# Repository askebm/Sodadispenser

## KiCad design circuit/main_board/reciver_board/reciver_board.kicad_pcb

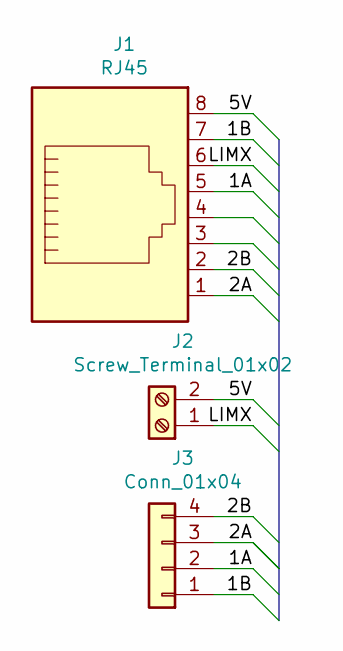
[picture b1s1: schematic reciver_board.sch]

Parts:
J1: RJ45; RJ45_Wuerth_7499010121A_Horizontal
J2: Screw_Terminal_01x02; TerminalBlock_Altech_AK300-2_P5.00mm
J3: Conn_01x04; PinSocket_1x04_P2.54mm_Vertical

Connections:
/1A: J1.5, J3.2
/1B: J1.7, J3.1
/2A: J1.1, J3.3
/2B: J1.2, J3.4
/5V: J1.8, J2.2
/LIMX: J1.6, J2.1

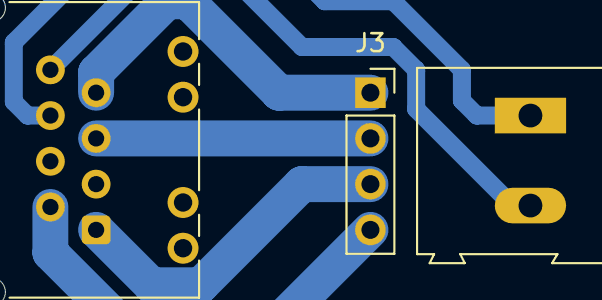
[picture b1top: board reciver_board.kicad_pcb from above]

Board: 2 copper layers, 3 parts (0 on the bottom side), 6 nets.

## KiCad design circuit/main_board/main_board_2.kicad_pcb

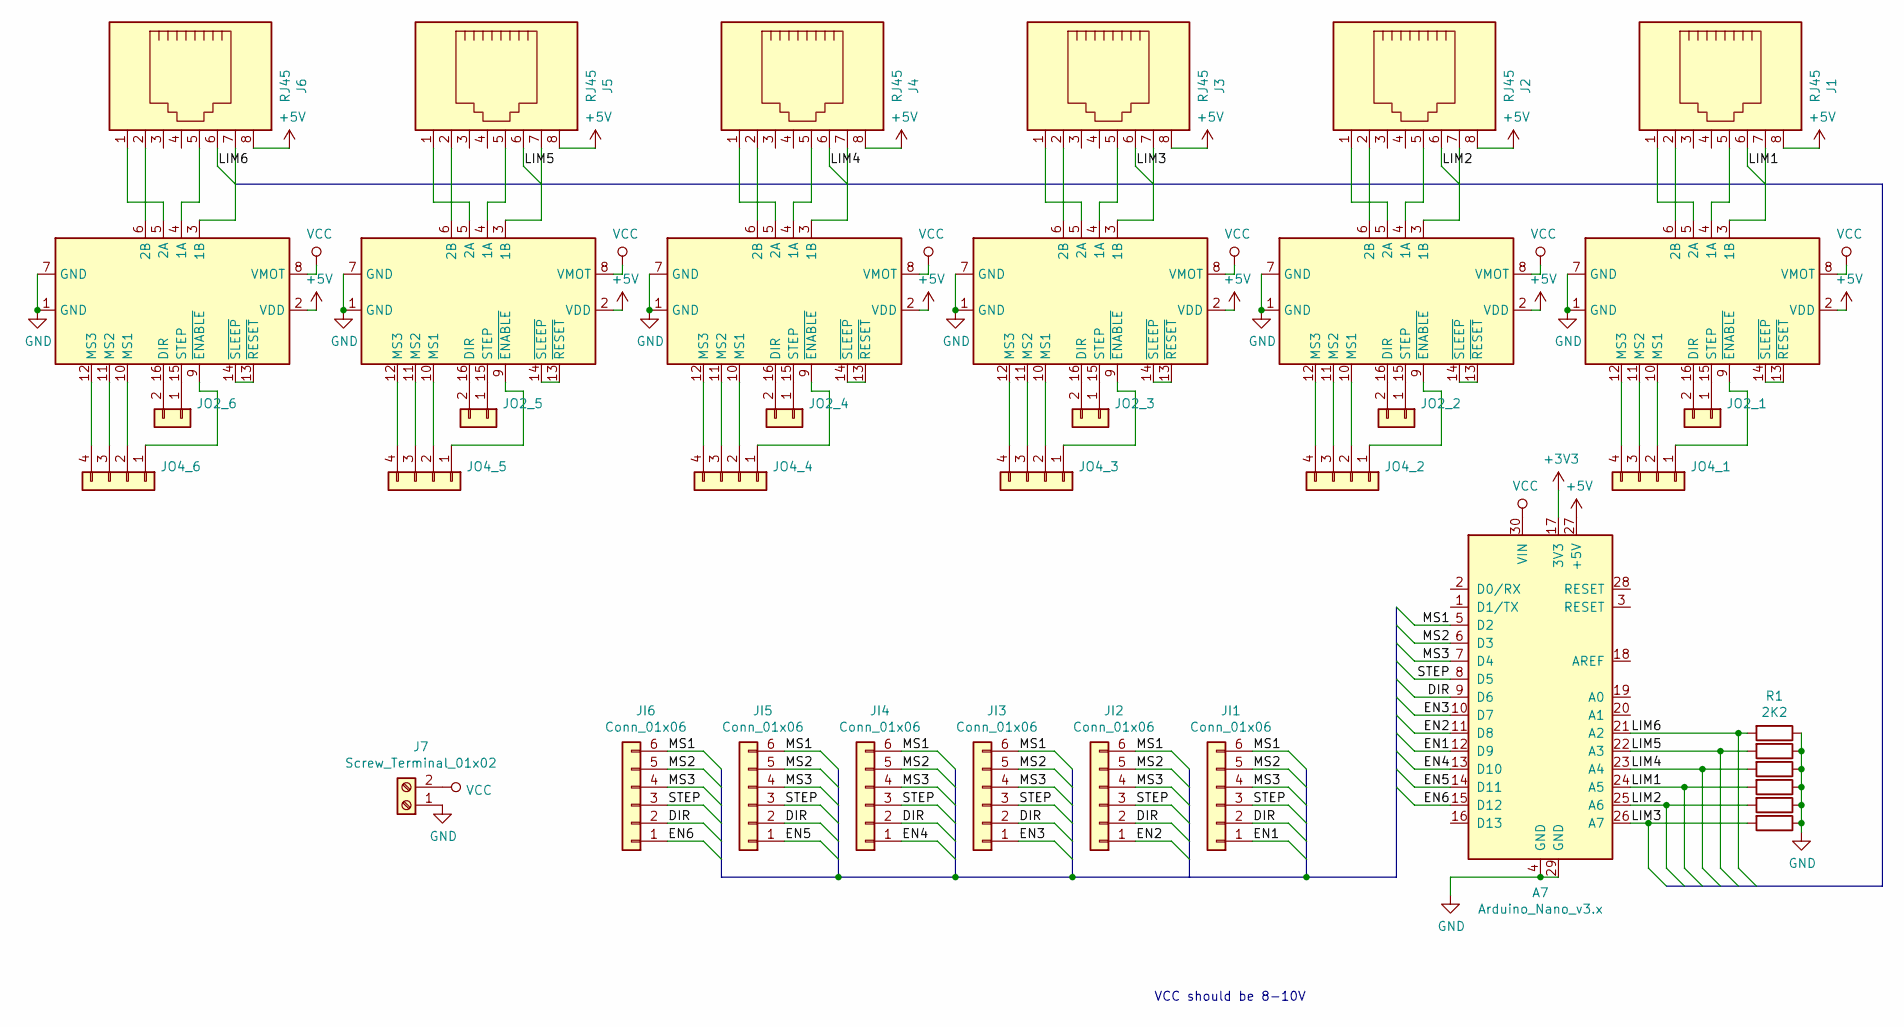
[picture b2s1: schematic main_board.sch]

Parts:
A1, A2, A3, A4, A5, A6: Pololu_Breakout_A4988; Pololu_Breakout-16_15.2x20.3mm
A7: Arduino_Nano_v3.x; Arduino_Nano
J1, J2, J3, J4, J5, J6: RJ45; RJ45_Wuerth_7499010121A_Horizontal
J7: Screw_Terminal_01x02; TerminalBlock_Altech_AK300-2_P5.00mm
JI1, JI2, JI3, JI4, JI5, JI6: Conn_01x06; PinHeader_1x06_P2.54mm_Vertical
JO2_1, JO2_2, JO2_3, JO2_4, JO2_5, JO2_6: Conn_01x02; PinHeader_1x02_P2.54mm_Vertical
JO4_1, JO4_2, JO4_3, JO4_4, JO4_5, JO4_6: Conn_01x04; PinHeader_1x04_P2.54mm_Vertical
R1, R2, R3, R4, R5, R6: 2K2; R_Axial_DIN0309_L9.0mm_D3.2mm_P15.24mm_Horizontal

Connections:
+5V: A1.2 (VDD), A2.2 (VDD), A3.2 (VDD), A4.2 (VDD), A5.2 (VDD), A6.2 (VDD), A7.27 (+5V), J1.8, J2.8, J3.8, J4.8, J5.8, J6.8
/DIR: A7.9 (D6), JI1.2, JI2.2, JI3.2, JI4.2, JI5.2, JI6.2
/EN1: A7.12 (D9), JI1.1
/EN2: A7.11 (D8), JI2.1
/EN3: A7.10 (D7), JI3.1
/EN4: A7.13 (D10), JI4.1
/EN5: A7.14 (D11), JI5.1
/EN6: A7.15 (D12), JI6.1
/LIM1: A7.24 (A5), J1.6, R4.2
/LIM2: A7.25 (A6), J2.6, R5.2
/LIM3: A7.26 (A7), J3.6, R6.2
/LIM4: A7.23 (A4), J4.6, R3.2
/LIM5: A7.22 (A3), J5.6, R2.2
/LIM6: A7.21 (A2), J6.6, R1.2
/MS1: A7.5 (D2), JI1.6, JI2.6, JI3.6, JI4.6, JI5.6, JI6.6
/MS2: A7.6 (D3), JI1.5, JI2.5, JI3.5, JI4.5, JI5.5, JI6.5
/MS3: A7.7 (D4), JI1.4, JI2.4, JI3.4, JI4.4, JI5.4, JI6.4
/STEP: A7.8 (D5), JI1.3, JI2.3, JI3.3, JI4.3, JI5.3, JI6.3
GND: A1.1 (GND), A1.7 (GND), A2.1 (GND), A2.7 (GND), A3.1 (GND), A3.7 (GND), A4.1 (GND), A4.7 (GND), A5.1 (GND), A5.7 (GND), A6.1 (GND), A6.7 (GND), A7.4 (GND), A7.29 (GND), J7.1, R1.1, R2.1, R3.1, R4.1, R5.1, R6.1
unnamed: A1.3 (1B), J1.7
unnamed: A1.4 (1A), J1.5
unnamed: A1.5 (2A), J1.1
unnamed: A1.6 (2B), J1.2
unnamed: A1.9 (~ENABLE), JO4_1.1
unnamed: A1.10 (MS1), JO4_1.2
unnamed: A1.11 (MS2), JO4_1.3
unnamed: A1.12 (MS3), JO4_1.4
unnamed: A1.13 (~RESET), A1.14 (~SLEEP)
unnamed: A1.15 (STEP), JO2_1.1
unnamed: A1.16 (DIR), JO2_1.2
unnamed: A2.3 (1B), J2.7
unnamed: A2.4 (1A), J2.5
unnamed: A2.5 (2A), J2.1
unnamed: A2.6 (2B), J2.2
unnamed: A2.9 (~ENABLE), JO4_2.1
unnamed: A2.10 (MS1), JO4_2.2
unnamed: A2.11 (MS2), JO4_2.3
unnamed: A2.12 (MS3), JO4_2.4
unnamed: A2.13 (~RESET), A2.14 (~SLEEP)
unnamed: A2.15 (STEP), JO2_2.1
unnamed: A2.16 (DIR), JO2_2.2
unnamed: A3.3 (1B), J3.7
unnamed: A3.4 (1A), J3.5
unnamed: A3.5 (2A), J3.1
unnamed: A3.6 (2B), J3.2
unnamed: A3.9 (~ENABLE), JO4_3.1
unnamed: A3.10 (MS1), JO4_3.2
unnamed: A3.11 (MS2), JO4_3.3
unnamed: A3.12 (MS3), JO4_3.4
unnamed: A3.13 (~RESET), A3.14 (~SLEEP)
unnamed: A3.15 (STEP), JO2_3.1
unnamed: A3.16 (DIR), JO2_3.2
unnamed: A4.3 (1B), J4.7
unnamed: A4.4 (1A), J4.5
unnamed: A4.5 (2A), J4.1
unnamed: A4.6 (2B), J4.2
unnamed: A4.9 (~ENABLE), JO4_4.1
unnamed: A4.10 (MS1), JO4_4.2
unnamed: A4.11 (MS2), JO4_4.3
unnamed: A4.12 (MS3), JO4_4.4
unnamed: A4.13 (~RESET), A4.14 (~SLEEP)
unnamed: A4.15 (STEP), JO2_4.1
unnamed: A4.16 (DIR), JO2_4.2
unnamed: A5.3 (1B), J5.7
unnamed: A5.4 (1A), J5.5
unnamed: A5.5 (2A), J5.1
unnamed: A5.6 (2B), J5.2
unnamed: A5.9 (~ENABLE), JO4_5.1
unnamed: A5.10 (MS1), JO4_5.2
unnamed: A5.11 (MS2), JO4_5.3
unnamed: A5.12 (MS3), JO4_5.4
unnamed: A5.13 (~RESET), A5.14 (~SLEEP)
unnamed: A5.15 (STEP), JO2_5.1
unnamed: A5.16 (DIR), JO2_5.2
unnamed: A6.3 (1B), J6.7
unnamed: A6.4 (1A), J6.5
unnamed: A6.5 (2A), J6.1
unnamed: A6.6 (2B), J6.2
unnamed: A6.9 (~ENABLE), JO4_6.1
unnamed: A6.10 (MS1), JO4_6.2
unnamed: A6.11 (MS2), JO4_6.3
unnamed: A6.12 (MS3), JO4_6.4
unnamed: A6.13 (~RESET), A6.14 (~SLEEP)
unnamed: A6.15 (STEP), JO2_6.1
unnamed: A6.16 (DIR), JO2_6.2
VCC: A1.8 (VMOT), A2.8 (VMOT), A3.8 (VMOT), A4.8 (VMOT), A5.8 (VMOT), A6.8 (VMOT), A7.30 (VIN), J7.2

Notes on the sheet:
VCC should be 8-10V

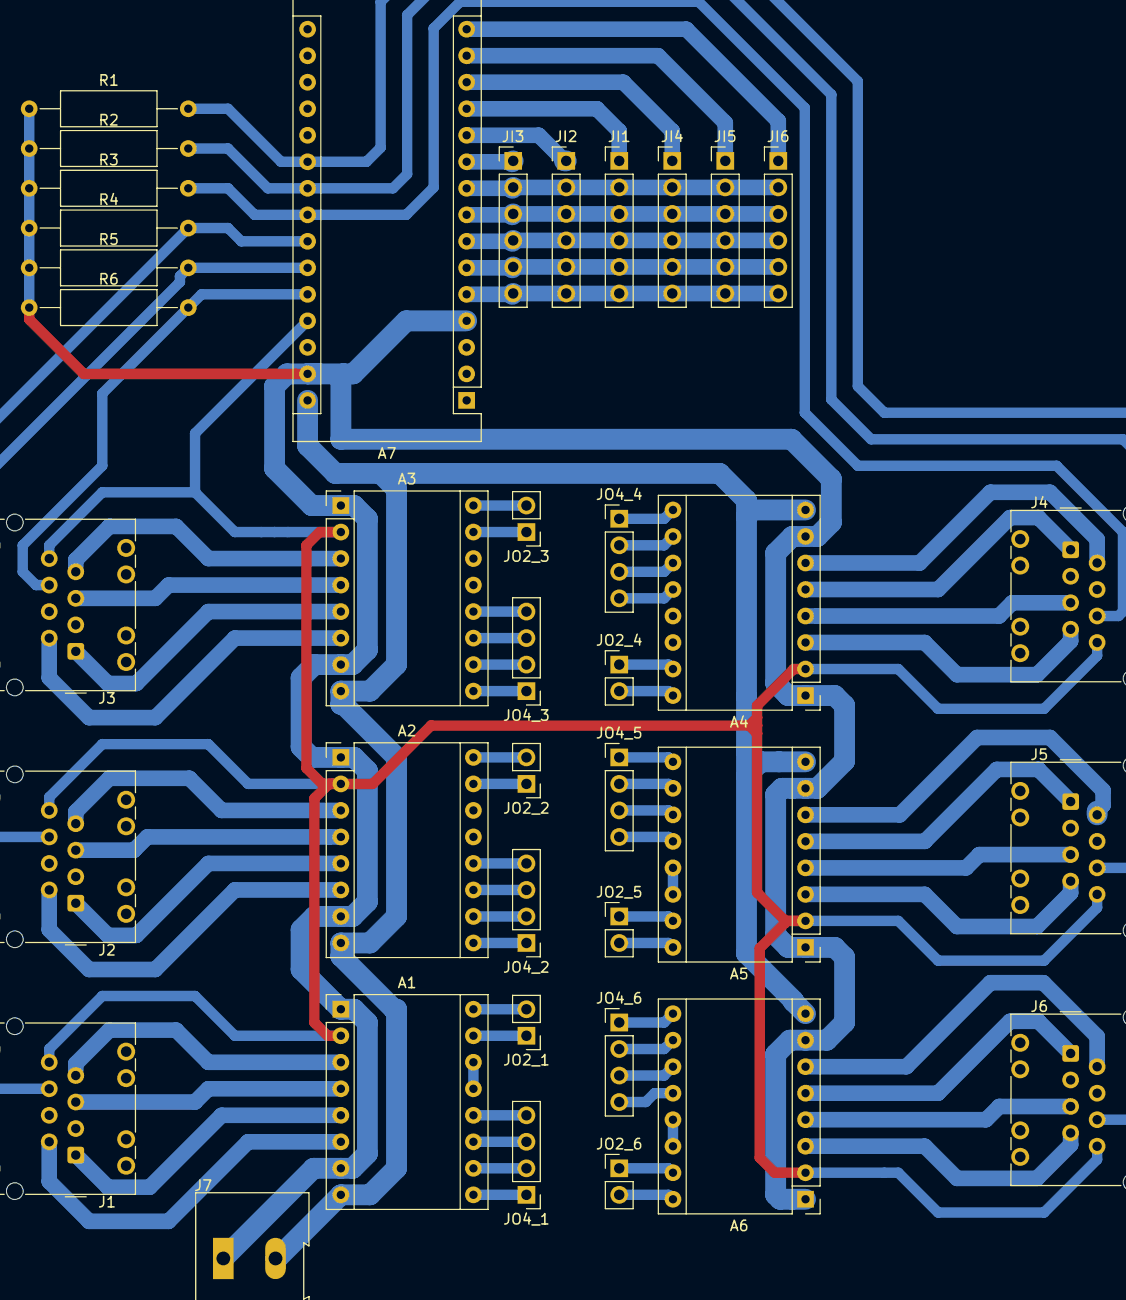
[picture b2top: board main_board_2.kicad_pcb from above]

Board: 2 copper layers, 38 parts (0 on the bottom side), 86 nets.

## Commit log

2018-11-25 Nearly done
2018-11-25 Need this
2018-11-25 Added picture
2018-11-25 Added readme
2018-11-25 removed file
2018-11-25 Fixed offset in stack_side
2018-11-25 Updated dxf file, moved rj45 socket
2018-11-26 Added circuit
2018-11-26 Second revision
2018-11-26 Startet work on 1 layer pcb
2018-11-27 Finnished a complete first revision of the circuits
2018-11-27 Fixed surfix
2018-11-28 Started work on collection ramp
2018-11-28 Fixed rj45 socket and a hole
2018-11-28 adjusted limit switch position
2018-11-28 Fixed motor position
2018-11-28 Adjusted lane size
2018-11-29 Removed connection from sleep and reset to 5v
